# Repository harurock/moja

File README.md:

# moja
http://hakase.ddo.jp/wp-content/uploads/2014/09/Screenshot_2014-09-07-19-07-31.png

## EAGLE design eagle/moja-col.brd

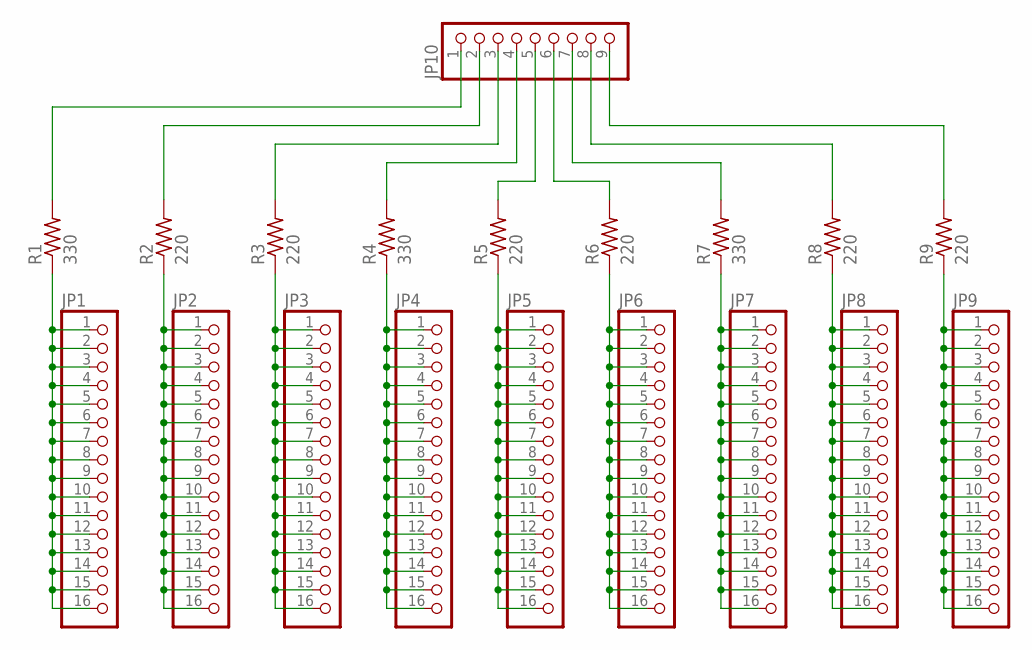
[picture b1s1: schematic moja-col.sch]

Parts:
JP1, JP2, JP3, JP4, JP5, JP6, JP7, JP8, JP9: PINHD-1X16; 1X16
JP10: PINHD-1X9; 1X09
R1, R4, R7: 330; 0204V
R2, R3, R5, R6, R8, R9: 220; 0204V

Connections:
unnamed: JP1.1, JP1.2, JP1.3, JP1.4, JP1.5, JP1.6, JP1.7, JP1.8, JP1.9, JP1.10, JP1.11, JP1.12, JP1.13, JP1.14, JP1.15, JP1.16, R1.1
unnamed: JP2.1, JP2.2, JP2.3, JP2.4, JP2.5, JP2.6, JP2.7, JP2.8, JP2.9, JP2.10, JP2.11, JP2.12, JP2.13, JP2.14, JP2.15, JP2.16, R2.1
unnamed: JP3.1, JP3.2, JP3.3, JP3.4, JP3.5, JP3.6, JP3.7, JP3.8, JP3.9, JP3.10, JP3.11, JP3.12, JP3.13, JP3.14, JP3.15, JP3.16, R3.1
unnamed: JP4.1, JP4.2, JP4.3, JP4.4, JP4.5, JP4.6, JP4.7, JP4.8, JP4.9, JP4.10, JP4.11, JP4.12, JP4.13, JP4.14, JP4.15, JP4.16, R4.1
unnamed: JP5.1, JP5.2, JP5.3, JP5.4, JP5.5, JP5.6, JP5.7, JP5.8, JP5.9, JP5.10, JP5.11, JP5.12, JP5.13, JP5.14, JP5.15, JP5.16, R5.1
unnamed: JP6.1, JP6.2, JP6.3, JP6.4, JP6.5, JP6.6, JP6.7, JP6.8, JP6.9, JP6.10, JP6.11, JP6.12, JP6.13, JP6.14, JP6.15, JP6.16, R6.1
unnamed: JP7.1, JP7.2, JP7.3, JP7.4, JP7.5, JP7.6, JP7.7, JP7.8, JP7.9, JP7.10, JP7.11, JP7.12, JP7.13, JP7.14, JP7.15, JP7.16, R7.1
unnamed: JP8.1, JP8.2, JP8.3, JP8.4, JP8.5, JP8.6, JP8.7, JP8.8, JP8.9, JP8.10, JP8.11, JP8.12, JP8.13, JP8.14, JP8.15, JP8.16, R8.1
unnamed: JP9.1, JP9.2, JP9.3, JP9.4, JP9.5, JP9.6, JP9.7, JP9.8, JP9.9, JP9.10, JP9.11, JP9.12, JP9.13, JP9.14, JP9.15, JP9.16, R9.1
unnamed: JP10.1, R1.2
unnamed: JP10.2, R2.2
unnamed: JP10.3, R3.2
unnamed: JP10.4, R4.2
unnamed: JP10.5, R5.2
unnamed: JP10.6, R6.2
unnamed: JP10.7, R7.2
unnamed: JP10.8, R8.2
unnamed: JP10.9, R9.2

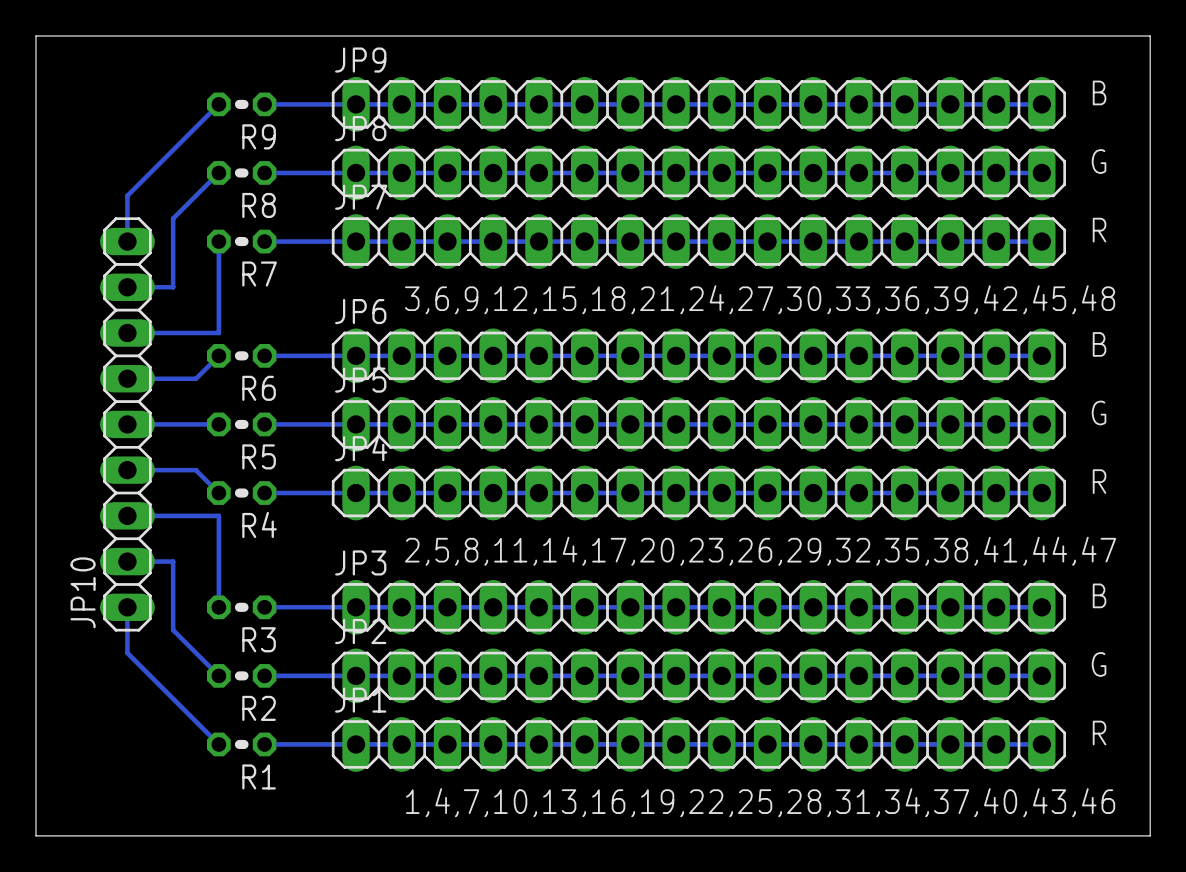
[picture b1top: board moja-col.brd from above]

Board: 2 copper layers, 61.9 x 44.4 mm, 19 parts (0 on the bottom side), 18 nets.

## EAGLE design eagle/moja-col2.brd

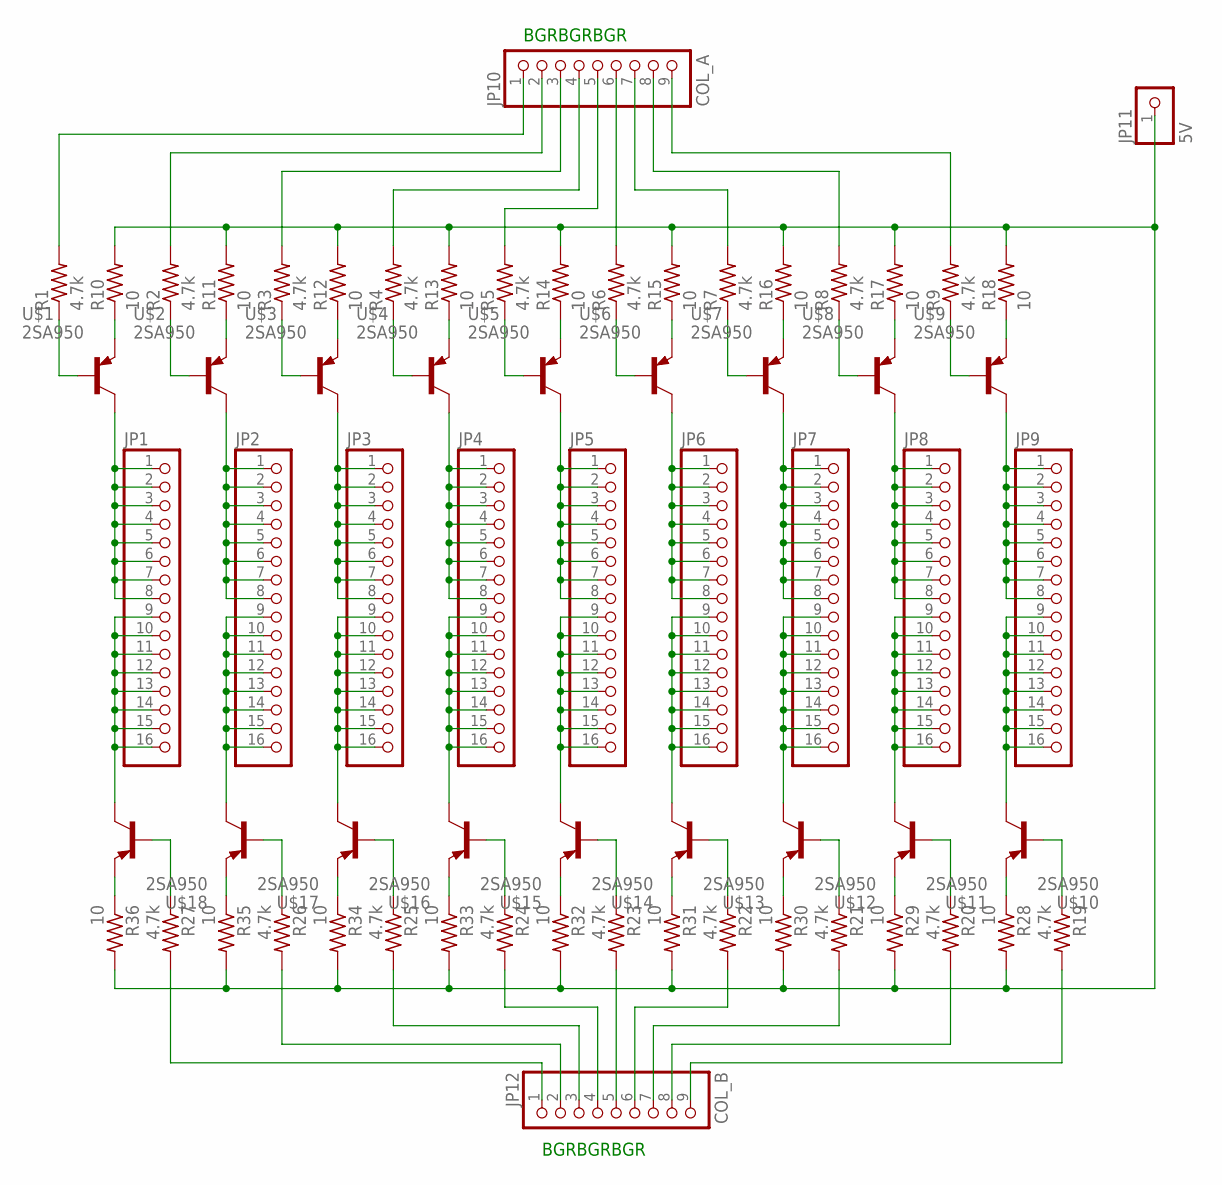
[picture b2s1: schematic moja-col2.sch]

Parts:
JP1, JP2, JP3, JP4, JP5, JP6, JP7, JP8, JP9: PINHD-1X16; 1X16
JP10: COL_A; 1X09
JP11: 5V; 1X01
JP12: COL_B; 1X09
R1, R2, R3, R4, R5, R6, R7, R8, R9, R19, R20, R21, R22, R23, R24, R25, R26, R27: 4.7k; 0204V
R10, R11, R12, R13, R14, R15, R16, R17, R18, R28, R29, R30, R31, R32, R33, R34, R35, R36: 10; 0204V
U$1, U$2, U$3, U$4, U$5, U$6, U$7, U$8, U$9, U$10, U$11, U$12, U$13, U$14, U$15, U$16, U$17, U$18: 2SA950; TO-92-AMMO

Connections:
unnamed: JP1.1, JP1.2, JP1.3, JP1.4, JP1.5, JP1.6, JP1.7, JP1.8, U$1.2 (C)
unnamed: JP2.1, JP2.2, JP2.3, JP2.4, JP2.5, JP2.6, JP2.7, JP2.8, U$2.2 (C)
unnamed: JP3.1, JP3.2, JP3.3, JP3.4, JP3.5, JP3.6, JP3.7, JP3.8, U$3.2 (C)
unnamed: JP4.1, JP4.2, JP4.3, JP4.4, JP4.5, JP4.6, JP4.7, JP4.8, U$4.2 (C)
unnamed: JP5.1, JP5.2, JP5.3, JP5.4, JP5.5, JP5.6, JP5.7, JP5.8, U$5.2 (C)
unnamed: JP6.1, JP6.2, JP6.3, JP6.4, JP6.5, JP6.6, JP6.7, JP6.8, U$6.2 (C)
unnamed: JP7.1, JP7.2, JP7.3, JP7.4, JP7.5, JP7.6, JP7.7, JP7.8, U$7.2 (C)
unnamed: JP8.1, JP8.2, JP8.3, JP8.4, JP8.5, JP8.6, JP8.7, JP8.8, U$8.2 (C)
unnamed: JP9.1, JP9.2, JP9.3, JP9.4, JP9.5, JP9.6, JP9.7, JP9.8, U$9.2 (C)
unnamed: JP10.1, R1.2
unnamed: JP10.2, R2.2
unnamed: JP10.3, R3.2
unnamed: JP10.4, R4.2
unnamed: JP10.5, R5.2
unnamed: JP10.6, R6.2
unnamed: JP10.7, R7.2
unnamed: JP10.8, R8.2
unnamed: JP10.9, R9.2
unnamed: JP1.9, JP1.10, JP1.11, JP1.12, JP1.13, JP1.14, JP1.15, JP1.16, U$18.2 (C)
unnamed: JP2.9, JP2.10, JP2.11, JP2.12, JP2.13, JP2.14, JP2.15, JP2.16, U$17.2 (C)
unnamed: JP3.9, JP3.10, JP3.11, JP3.12, JP3.13, JP3.14, JP3.15, JP3.16, U$16.2 (C)
unnamed: JP4.9, JP4.10, JP4.11, JP4.12, JP4.13, JP4.14, JP4.15, JP4.16, U$15.2 (C)
unnamed: JP5.9, JP5.10, JP5.11, JP5.12, JP5.13, JP5.14, JP5.15, JP5.16, U$14.2 (C)
unnamed: JP6.9, JP6.10, JP6.11, JP6.12, JP6.13, JP6.14, JP6.15, JP6.16, U$13.2 (C)
unnamed: JP7.9, JP7.10, JP7.11, JP7.12, JP7.13, JP7.14, JP7.15, JP7.16, U$12.2 (C)
unnamed: JP8.9, JP8.10, JP8.11, JP8.12, JP8.13, JP8.14, JP8.15, JP8.16, U$11.2 (C)
unnamed: JP9.9, JP9.10, JP9.11, JP9.12, JP9.13, JP9.14, JP9.15, JP9.16, U$10.2 (C)
unnamed: R1.1, U$1.3 (B)
unnamed: R2.1, U$2.3 (B)
unnamed: R3.1, U$3.3 (B)
unnamed: R4.1, U$4.3 (B)
unnamed: R5.1, U$5.3 (B)
unnamed: R6.1, U$6.3 (B)
unnamed: R7.1, U$7.3 (B)
unnamed: R8.1, U$8.3 (B)
unnamed: R9.1, U$9.3 (B)
unnamed: R10.1, U$1.1 (E)
unnamed: R11.1, U$2.1 (E)
unnamed: R12.1, U$3.1 (E)
unnamed: R13.1, U$4.1 (E)
unnamed: R14.1, U$5.1 (E)
unnamed: R15.1, U$6.1 (E)
unnamed: R16.1, U$7.1 (E)
unnamed: R17.1, U$8.1 (E)
unnamed: R18.1, U$9.1 (E)
unnamed: JP12.4, R24.2
unnamed: JP12.9, R19.2
unnamed: JP12.8, R20.2
unnamed: JP12.7, R21.2
unnamed: JP12.6, R22.2
unnamed: JP12.5, R23.2
unnamed: JP12.3, R25.2
unnamed: JP12.2, R26.2
unnamed: JP12.1, R27.2
unnamed: R19.1, U$10.3 (B)
unnamed: R20.1, U$11.3 (B)
unnamed: R21.1, U$12.3 (B)
unnamed: R22.1, U$13.3 (B)
unnamed: R23.1, U$14.3 (B)
unnamed: R24.1, U$15.3 (B)
unnamed: R25.1, U$16.3 (B)
unnamed: R26.1, U$17.3 (B)
unnamed: R27.1, U$18.3 (B)
unnamed: JP11.1, R10.2, R11.2, R12.2, R13.2, R14.2, R15.2, R16.2, R17.2, R18.2, R28.2, R29.2, R30.2, R31.2, R32.2, R33.2, R34.2, R35.2, R36.2
unnamed: R28.1, U$10.1 (E)
unnamed: R29.1, U$11.1 (E)
unnamed: R30.1, U$12.1 (E)
unnamed: R31.1, U$13.1 (E)
unnamed: R32.1, U$14.1 (E)
unnamed: R33.1, U$15.1 (E)
unnamed: R34.1, U$16.1 (E)
unnamed: R35.1, U$17.1 (E)
unnamed: R36.1, U$18.1 (E)

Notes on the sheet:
BGRBGRBGR

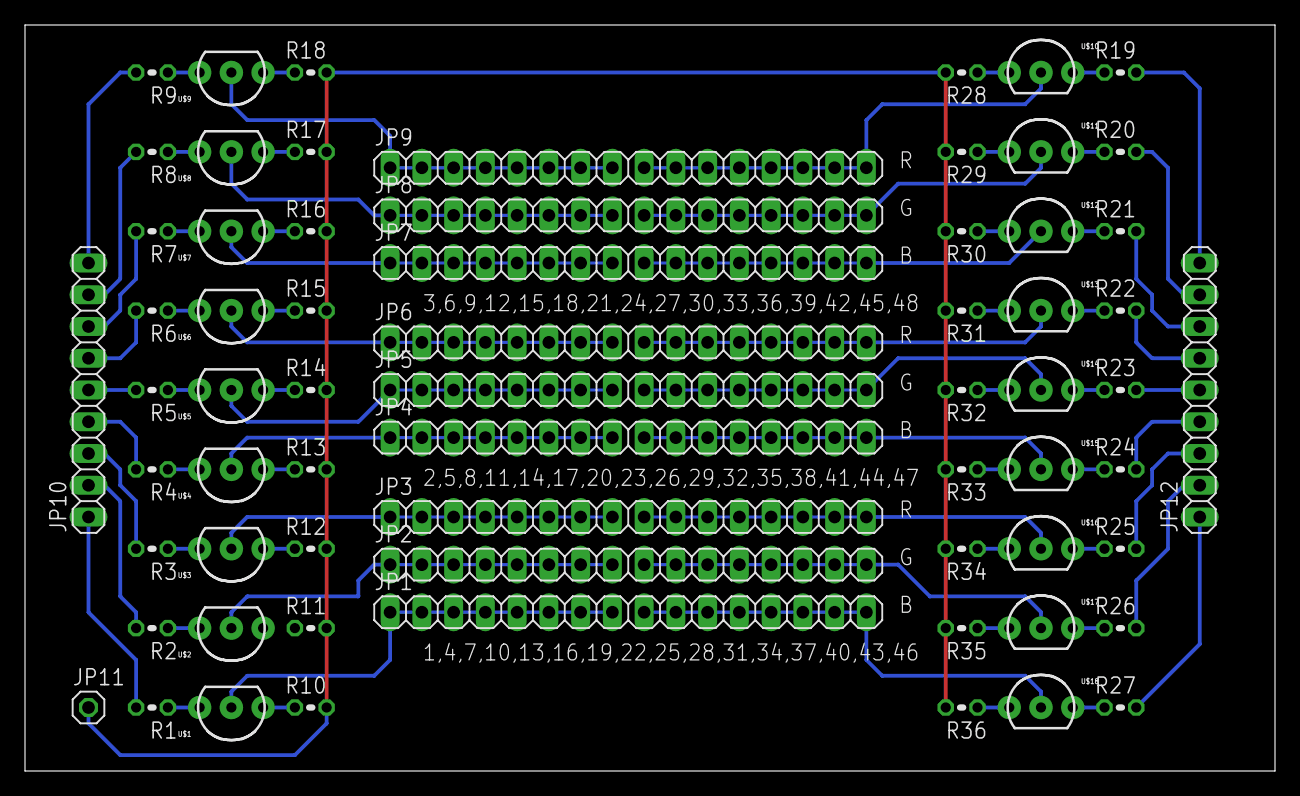
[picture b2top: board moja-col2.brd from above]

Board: 2 copper layers, 100.0 x 59.7 mm, 66 parts (0 on the bottom side), 73 nets.

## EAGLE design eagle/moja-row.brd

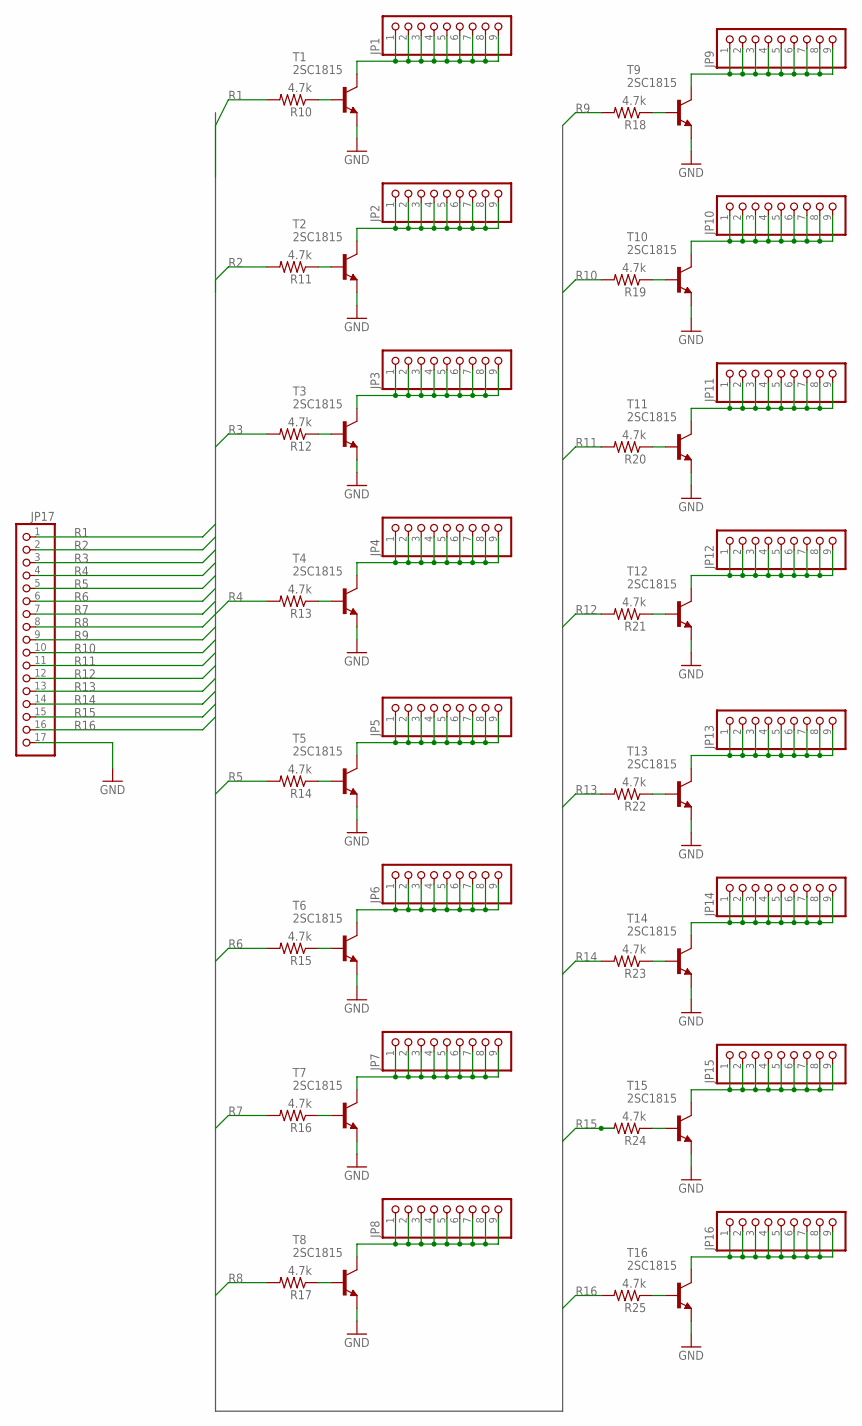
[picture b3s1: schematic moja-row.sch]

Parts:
JP1, JP2, JP3, JP4, JP5, JP6, JP7, JP8, JP9, JP10, JP11, JP12, JP13, JP14, JP15, JP16: PINHD-1X9; 1X09
JP17: PINHD-1X17; 1X17
R10, R11, R12, R13, R14, R15, R16, R17, R18, R19, R20, R21, R22, R23, R24, R25: 4.7k; 0204V
T1, T2, T3, T4, T5, T6, T7, T8, T9, T10, T11, T12, T13, T14, T15, T16: 2SC1815; TO92-ECB

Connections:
GND: JP17.17, T1.E, T2.E, T3.E, T4.E, T5.E, T6.E, T7.E, T8.E, T9.E, T10.E, T11.E, T12.E, T13.E, T14.E, T15.E, T16.E
unnamed: JP1.1, JP1.2, JP1.3, JP1.4, JP1.5, JP1.6, JP1.7, JP1.8, JP1.9, T1.C
unnamed: R10.1, T1.B
unnamed: JP2.1, JP2.2, JP2.3, JP2.4, JP2.5, JP2.6, JP2.7, JP2.8, JP2.9, T2.C
unnamed: R11.1, T2.B
unnamed: JP3.1, JP3.2, JP3.3, JP3.4, JP3.5, JP3.6, JP3.7, JP3.8, JP3.9, T3.C
unnamed: R12.1, T3.B
unnamed: JP4.1, JP4.2, JP4.3, JP4.4, JP4.5, JP4.6, JP4.7, JP4.8, JP4.9, T4.C
unnamed: R13.1, T4.B
unnamed: JP5.1, JP5.2, JP5.3, JP5.4, JP5.5, JP5.6, JP5.7, JP5.8, JP5.9, T5.C
unnamed: R14.1, T5.B
unnamed: JP6.1, JP6.2, JP6.3, JP6.4, JP6.5, JP6.6, JP6.7, JP6.8, JP6.9, T6.C
unnamed: R15.1, T6.B
unnamed: JP7.1, JP7.2, JP7.3, JP7.4, JP7.5, JP7.6, JP7.7, JP7.8, JP7.9, T7.C
unnamed: R16.1, T7.B
unnamed: JP8.1, JP8.2, JP8.3, JP8.4, JP8.5, JP8.6, JP8.7, JP8.8, JP8.9, T8.C
unnamed: R17.1, T8.B
unnamed: JP9.1, JP9.2, JP9.3, JP9.4, JP9.5, JP9.6, JP9.7, JP9.8, JP9.9, T9.C
unnamed: R18.1, T9.B
unnamed: JP10.1, JP10.2, JP10.3, JP10.4, JP10.5, JP10.6, JP10.7, JP10.8, JP10.9, T10.C
unnamed: R19.1, T10.B
unnamed: JP11.1, JP11.2, JP11.3, JP11.4, JP11.5, JP11.6, JP11.7, JP11.8, JP11.9, T11.C
unnamed: R20.1, T11.B
unnamed: JP12.1, JP12.2, JP12.3, JP12.4, JP12.5, JP12.6, JP12.7, JP12.8, JP12.9, T12.C
unnamed: R21.1, T12.B
unnamed: JP13.1, JP13.2, JP13.3, JP13.4, JP13.5, JP13.6, JP13.7, JP13.8, JP13.9, T13.C
unnamed: R22.1, T13.B
unnamed: JP14.1, JP14.2, JP14.3, JP14.4, JP14.5, JP14.6, JP14.7, JP14.8, JP14.9, T14.C
unnamed: R23.1, T14.B
unnamed: JP15.1, JP15.2, JP15.3, JP15.4, JP15.5, JP15.6, JP15.7, JP15.8, JP15.9, T15.C
unnamed: R24.1, T15.B
unnamed: JP16.1, JP16.2, JP16.3, JP16.4, JP16.5, JP16.6, JP16.7, JP16.8, JP16.9, T16.C
unnamed: R25.1, T16.B
R1: JP17.1, R10.2
R2: JP17.2, R11.2
R3: JP17.3, R12.2
R4: JP17.4, R13.2
R5: JP17.5, R14.2
R6: JP17.6, R15.2
R7: JP17.7, R16.2
R8: JP17.8, R17.2
R9: JP17.9, R18.2
R10: JP17.10, R19.2
R11: JP17.11, R20.2
R12: JP17.12, R21.2
R13: JP17.13, R22.2
R14: JP17.14, R23.2
R15: JP17.15, R24.2
R16: JP17.16, R25.2

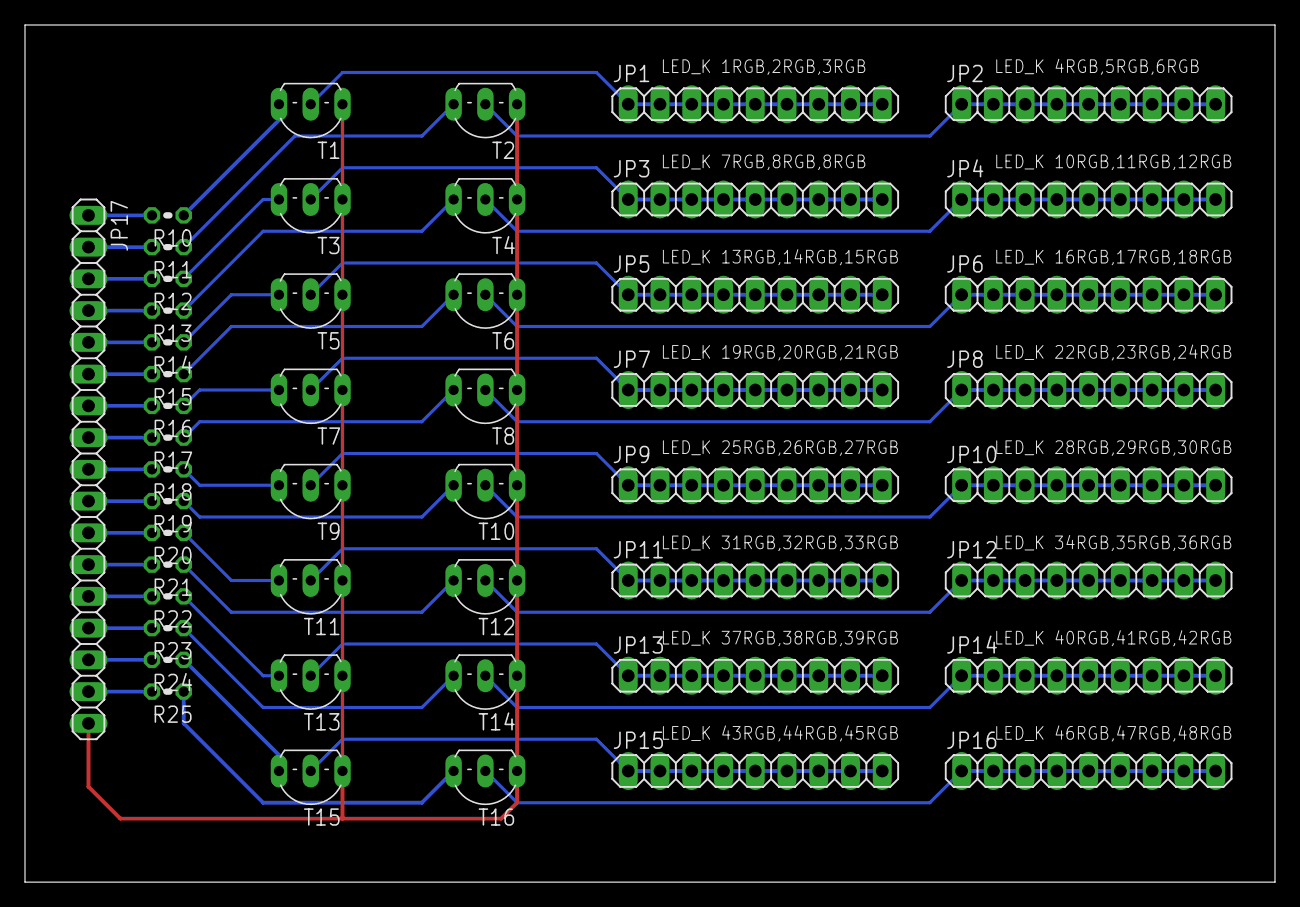
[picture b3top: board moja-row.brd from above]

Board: 2 copper layers, 100.0 x 68.6 mm, 49 parts (0 on the bottom side), 49 nets.

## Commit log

2015-07-31 Import from bitbucket

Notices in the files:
parts and their libraries:
nyaro: Licensing: CC v3.0 Share-Alike You are welcome to use this library for commercial purposes.
